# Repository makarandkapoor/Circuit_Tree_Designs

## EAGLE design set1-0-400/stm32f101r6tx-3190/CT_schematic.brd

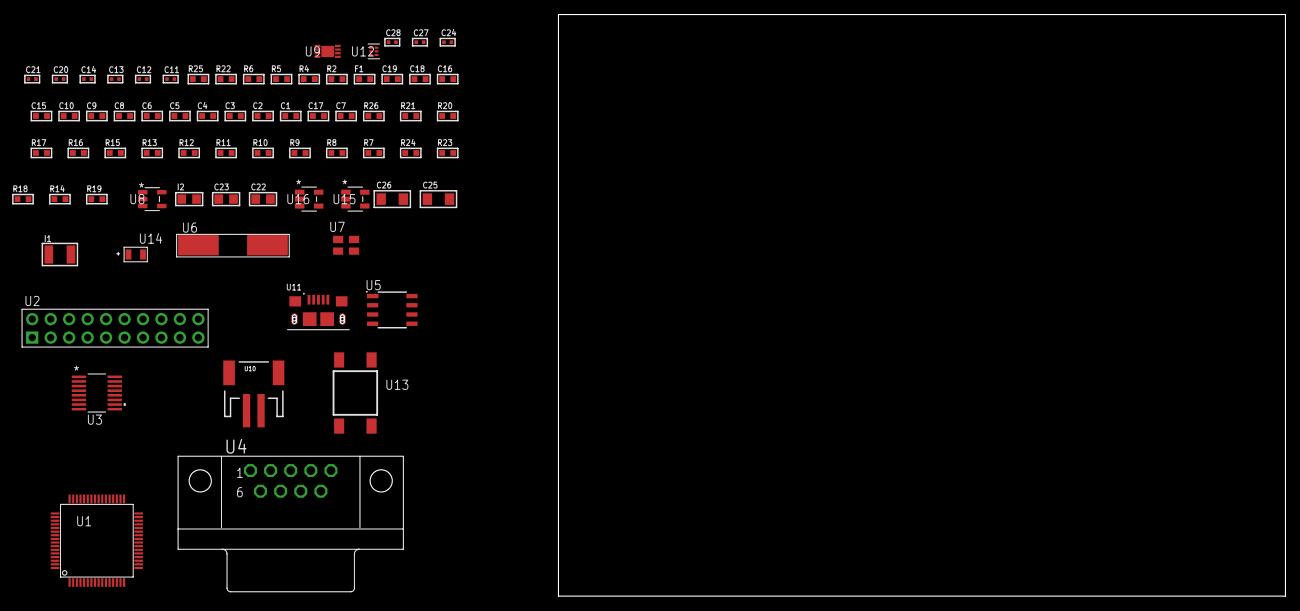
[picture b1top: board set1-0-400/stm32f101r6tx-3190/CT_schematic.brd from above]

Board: 2 copper layers, 71 parts (0 on the bottom side), 44 nets, no tracks yet.

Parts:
C1, C10, C15, C16, C18, C19: 1e-06; C0603
C2, C3, C4, C5, C6: 1e-07; C0603
C7: 4.7e-06; C0603
C8, C9: 1e-08; C0603
C11, C12: 1e-11; C0402
C13, C14, C24: 1e-07; C0402
C17: 2.2e-07; C0603
C20, C21, C27, C28: 1e-08; C0402
C22, C23: 1e-05; C0805
C25, C26: 1e-05; C1206
F1: 240.0; L0603
I1: 1e-05; L1210
I2: 2.2e-06; L0805
R2: 1000.0; R0603
R4: 4700.0; R0603
R5, R6: 2200.0; R0603
R7, R8, R9, R10, R11, R12, R13, R15, R16, R17, R20, R21, R26: 10000.0; R0603
R14: 100000.0; R0603
R18: 220000.0; R0603
R19: 1000000.0; R0603
R22: 9100.0; R0603
R23: 680000.0; R0603
R24: 120000.0; R0603
R25: 2000.0; R0603
U1: STM32F101R6T6; LQFP64
U2: TST-110-05-T-D-RA
U3: LTC2804CGN-1#PBF; SSOP-16
U4: 182-009-113R531; 182-009-MALE
U5: 24AA1025T-I/SN; SOIC-8
U6: ABLS-25.000MHZ-B2F-T
U7: ASEK-32.768KHz-ECST; ASEK
U8: ltc3406es5; TSOT-23-5
U9: MCP73831T-2ACI/MC; DFN8_2X3MC
U10: S2B-PH-SM4-TB(LF)(SN); JST-2-SMD
U11: 10118193-0001LF; FCI_10118193-0001LF
U12: TPS3895ADRYR; SON-6
U13: 4-1437565-2; SW_4-1437565-2
U14: Q65110A2395; LGM67K-G1J2-24-Z
U15, U16: nc7sz125m5x; NC7SZ125M5X

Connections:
CLK_CRYSTAL_U1_5: C11.1, U1.5, U6.1
CLK_CRYSTAL_U1_6: C12.1, U1.6, U6.2
CLK_U1_3: U1.3, U7.3
GND: C1.2, C2.2, C3.2, C4.2, C5.2, C6.2, C7.2, C8.2, C9.2, C10.2, C11.2, C12.2, C13.2, C14.2, C15.2, C16.2, C18.2, C19.2, C20.2, C21.2, C22.2, C23.1, C23.2, C24.2, C25.2, C26.2, C27.2, C28.2, R2.2, R7.2, R13.2, R16.2, R18.2, R22.2, R24.2, R25.2, U1.12, U1.18, U1.31, U1.47, U1.63, U2.4, U2.6, U2.8, U2.10, U2.12, U2.14, U2.16, U2.18, U2.20, U3.8, U4.5, U5.4, U5.7, U7.2, U8.2, U9.6, U9.9, U10.2, U11.5, U11.6, U11.7, U11.8, U11.9, U12.2, U14.C, U15.2, U15.3, U16.1, U16.3
INPUT_USBPOWER_5V: C25.1, R26.2, U9.1, U9.2, U11.1
NET_U1_7: R4.1, U1.7, U16.4
NET_U1_13: C8.1, C9.1, C10.1, F1.1, U1.13
NET_U1_58: R5.1, U1.58, U5.6
NET_U1_59: R6.1, U1.59, U5.5
NET_U1_60: R7.1, U1.60
NET_U1_62: U13.3, U13.4
NET_U2_3: R8.1, U2.3
NET_U2_7: R10.1, U2.7
NET_U2_9: R11.1, U2.9
NET_U2_19: R13.1, U2.19
NET_U3_6: C15.1, U3.6
NET_U3_7: C17.1, I1.2, U3.7
NET_U3_9: C16.1, U3.9
NET_U3_10: C17.2, U3.10
NET_U3_11: R14.1, U3.11
NET_U4_2: U3.1, U4.2
NET_U4_3: U3.3, U4.3
NET_U4_7: U3.2, U4.7
NET_U4_8: U3.4, U4.8
NET_U5_1: R16.1, U5.1
NET_U5_2: R17.1, U5.2
NET_U5_3: R15.1, U5.3
NET_U8_3: I2.1, U8.3
NET_U8_5: R18.1, R19.1, U8.5
NET_U8_ATNET_3: I2.2, R19.2
NET_U9_5: R26.1, U9.5
NET_U9_8: R25.1, U9.8
NET_U12_1: R21.1, R22.1, U12.1
NET_U12_3: R23.2, R24.1, U12.3
NET_U12_4: R20.1, U12.4, U15.4, U16.2
NET_U13_1: R2.1, U13.1, U13.2
PROC_SYS_JTDI: R9.1, U1.50, U2.5
PROC_SYS_JTDO_TRACESWO: U1.55, U2.13
PROC_USART1_CTS: U1.44, U3.13
PROC_USART1_RX: U1.43, U3.16
PROC_USART1_TX: U1.42, U3.14
RST_OUT_U2_SRESET_B: R12.1, U2.15, U15.1
VCC_S1_3V7: C22.1, C26.1, U8.4, U9.3, U9.4, U10.1
VCC_TIER1_3V3: C1.1, C2.1, C3.1, C4.1, C5.1, C6.1, C7.1, C13.1, C14.1, C18.1, C19.1, C20.1, C21.1, C23.2, C24.1, C27.1, C28.1, F1.2, I1.1, I2.2, R4.2, R5.2, R6.2, R8.2, R9.2, R10.2, R11.2, R12.2, R14.2, R15.2, R17.2, R19.2, R20.2, R21.2, R23.1, U1.1, U1.19, U1.32, U1.48, U1.64, U2.1, U2.2, U3.5, U3.12, U5.8, U7.4, U12.6, U15.5, U16.5

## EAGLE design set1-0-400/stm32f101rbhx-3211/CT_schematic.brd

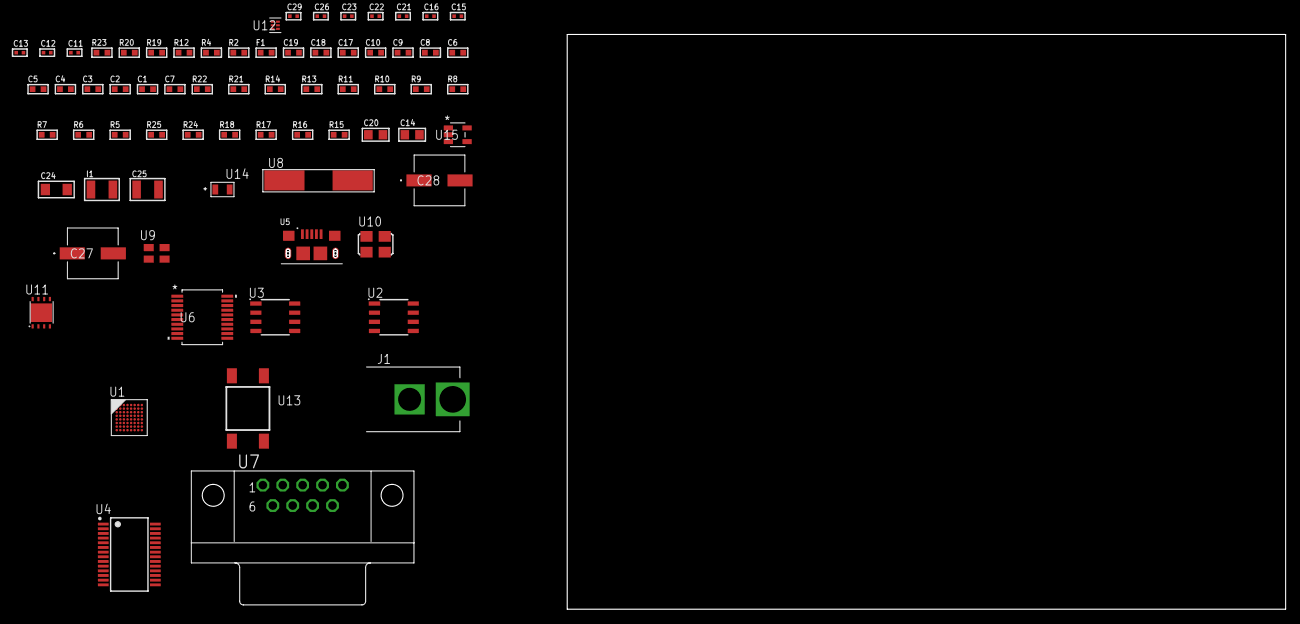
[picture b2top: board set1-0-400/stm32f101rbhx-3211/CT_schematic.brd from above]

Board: 2 copper layers, 70 parts (0 on the bottom side), 55 nets, no tracks yet.

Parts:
C1, C10, C17, C18, C19: 1e-06; C0603
C2, C3, C4, C5, C6: 1e-07; C0603
C7: 4.7e-06; C0603
C8, C9: 1e-08; C0603
C11, C12, C21, C22, C23, C29: 1e-08; C0402
C13, C15, C16, C26: 1e-07; C0402
C14, C20: 4.7e-06; C0805
C24: 1e-05; C1206
C25: 1e-05; C1210
C27, C28: 0.0001; EXV-9H
F1: 240.0; L0603
I1: 1.5e-05; L1210
J1: PJ-037B; PJ-037B_PACKAGE
R2, R20: 1000.0; R0603
R4, R12: 4700.0; R0603
R5, R6, R7, R8, R9, R10, R11, R13, R14, R21, R22: 10000.0; R0603
R15, R16, R17, R18: 100000.0; R0603
R19: 2231.0; R0603
R23: 9100.0; R0603
R24: 680000.0; R0603
R25: 120000.0; R0603
U1: STM32F101RBH6; TFBGA64
U2: AT25010B-SSHL-T; SOIC-8
U3: AT25M01-SSHM-T; SOIC-8
U4: FT232RL-REEL; SSOP-28
U5: 10118193-0001LF; FCI_10118193-0001LF
U6: MAX3218EAP+T; SSOP-20
U7: 182-009-113R531; 182-009-MALE
U8: ABLS-12.000MHZ-B4-T
U9: ASEK-32.768KHz-ECST; ASEK
U10: ASFL1-25MHZ-NCS; ASFL1
U11: LP3878SDX-ADJ/NOPB; WSON-8
U12: TPS3895ADRYR; SON-6
U13: 4-1437565-2; SW_4-1437565-2
U14: Q65110A2395; LGM67K-G1J2-24-Z
U15: nc7sz125m5x; NC7SZ125M5X

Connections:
CLK_CRYSTAL_U4_27: U4.27, U8.1
CLK_CRYSTAL_U4_28: U4.28, U8.2
CLK_U1_A1: U1.A1, U9.3
CLK_U1_C1: U1.C1, U10.3
GND: C1.2, C2.2, C3.2, C4.2, C5.2, C6.2, C7.2, C8.2, C9.2, C10.2, C11.2, C12.2, C13.2, C14.2, C15.2, C16.2, C17.2, C18.2, C19.2, C21.2, C22.2, C23.2, C24.2, C25.2, C26.2, C27.2, C28.2, C29.2, J1.2, R2.2, R5.2, R14.2, R20.2, R23.2, R25.2, U1.C2, U1.D4, U1.D5, U1.D6, U1.F1, U2.4, U3.4, U4.7, U4.18, U4.21, U4.25, U4.26, U5.5, U5.6, U5.7, U5.8, U5.9, U6.5, U6.17, U6.20, U7.5, U9.2, U10.2, U11.3, U11.PAD, U12.2, U14.C, U15.1, U15.3
NET_U1_B4: R5.1, U1.B4
NET_U1_E1: R4.1, U1.E1, U15.4
NET_U1_H1: C8.1, C9.1, C10.1, F1.1, U1.G1, U1.H1
NET_U1_H7: U13.3, U13.4
NET_U2_3: R6.1, U2.3
NET_U2_7: R8.1, U2.7
NET_U3_3: R9.1, U3.3
NET_U3_7: R11.1, U3.7
NET_U4_14: R13.1, U4.14
NET_U4_17: C15.1, U4.17
NET_U4_19: R14.1, U4.19
NET_U5_1: R12.1, U5.1
NET_U5_2: U4.16, U5.2
NET_U5_3: U4.15, U5.3
NET_U6_1: I1.1, U6.1
NET_U6_2: R15.1, U6.2
NET_U6_3: R16.1, U6.3
NET_U6_4: R17.1, U6.4
NET_U6_15: C19.1, U6.15
NET_U6_16: C20.2, U6.16
NET_U6_18: C20.1, U6.18
NET_U6_19: C18.1, U6.19
NET_U7_2: U6.12, U7.2
NET_U7_3: U6.14, U7.3
NET_U7_7: U6.11, U7.7
NET_U7_8: U6.13, U7.8
NET_U11_1: C23.1, U11.1
NET_U11_6: R19.2, R20.1, U11.6
NET_U11_8: R18.1, U11.8
NET_U12_1: R22.1, R23.1, U12.1
NET_U12_3: R24.2, R25.1, U12.3
NET_U12_4: R21.1, U12.4, U15.2
NET_U13_1: R2.1, U13.1, U13.2
PROC_SPI1_MISO: U1.A4, U3.2
PROC_SPI1_MOSI: U1.C4, U3.5
PROC_SPI1_NSS: R10.1, U1.A6, U3.1
PROC_SPI1_SCK: U1.A5, U3.6
PROC_SPI2_MISO: U1.F8, U2.2
PROC_SPI2_MOSI: U1.F7, U2.5
PROC_SPI2_NSS: R7.1, U1.H8, U2.1
PROC_SPI2_SCK: U1.G8, U2.6
PROC_USART1_CTS: U1.C8, U6.8
PROC_USART1_RX: U1.C3, U6.9
PROC_USART1_TX: U1.C7, U6.7
PROC_USART2_CTS: U1.G2, U4.3
PROC_USART2_RTS: U1.H2, U4.11
PROC_USART2_RX: U1.G3, U4.1
PROC_USART2_TX: U1.F3, U4.5
VCC_S1_7V2: C24.1, C27.1, C28.1, J1.1, R18.2, U11.4
VCC_TIER1_3V3: C1.1, C2.1, C3.1, C4.1, C5.1, C6.1, C7.1, C11.1, C12.1, C13.1, C14.1, C16.1, C17.1, C21.1, C22.1, C25.1, C26.1, C29.1, F1.2, I1.2, R4.2, R6.2, R7.2, R8.2, R9.2, R10.2, R11.2, R13.2, R15.2, R16.2, R17.2, R19.1, R21.2, R22.2, R24.1, U1.B2, U1.D2, U1.E4, U1.E5, U1.E6, U2.8, U3.8, U4.4, U4.20, U6.6, U9.4, U10.4, U11.5, U12.6, U15.5

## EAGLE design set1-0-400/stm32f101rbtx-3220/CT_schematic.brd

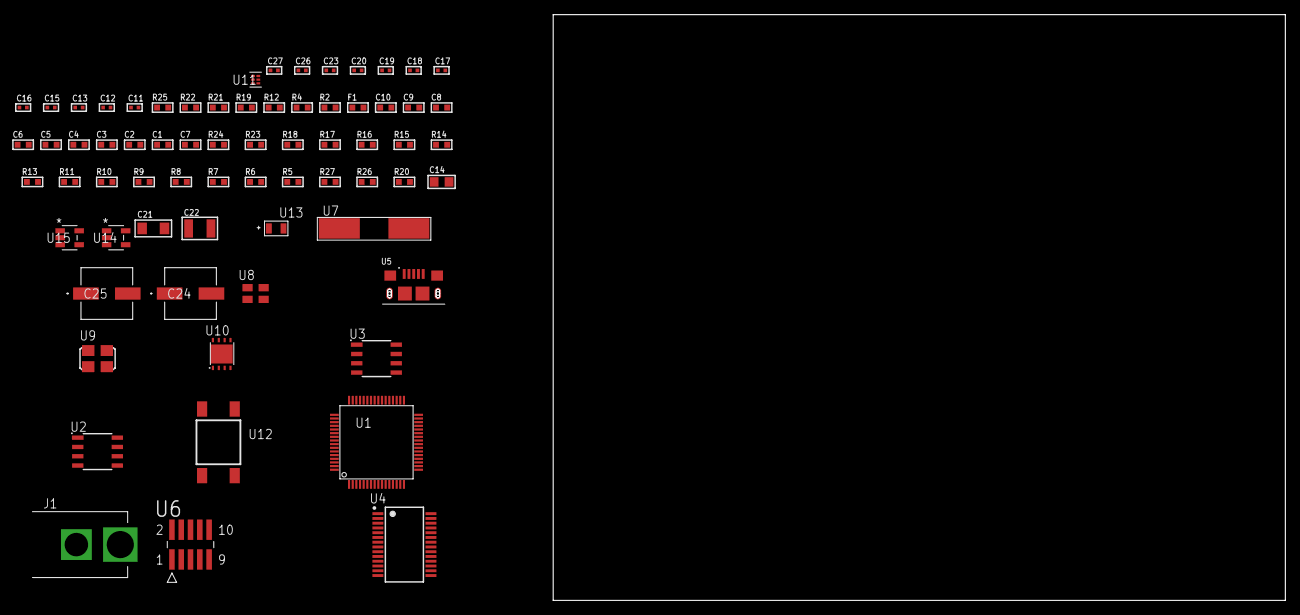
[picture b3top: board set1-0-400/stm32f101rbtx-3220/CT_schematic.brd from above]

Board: 2 copper layers, 122.6 x 80.0 mm, 69 parts (0 on the bottom side), 45 nets, no tracks yet.

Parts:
C1, C10: 1e-06; C0603
C2, C3, C4, C5, C6: 1e-07; C0603
C7: 4.7e-06; C0603
C8, C9: 1e-08; C0603
C11, C12, C18, C19, C20, C26, C27: 1e-08; C0402
C13, C15, C16, C17, C23: 1e-07; C0402
C14: 4.7e-06; C0805
C21: 1e-05; C1206
C22: 1e-05; C1210
C24, C25: 0.0001; EXV-9H
F1: 240.0; L0603
J1: PJ-037B; PJ-037B_PACKAGE
R2, R22: 1000.0; R0603
R4, R12: 4700.0; R0603
R5, R6, R7, R8, R9, R10, R11, R13, R14, R15, R16, R17, R18, R23, R24: 10000.0; R0603
R19: 5.0; R0603
R20: 100000.0; R0603
R21: 2231.0; R0603
R25: 9100.0; R0603
R26: 680000.0; R0603
R27: 120000.0; R0603
U1: STM32F101RBT6; LQFP64
U2: AT25020B-SSHL-T; SOIC-8
U3: AT25040B-SSHL-T; SOIC-8
U4: FT232RL-REEL; SSOP-28
U5: 10118193-0001LF; FCI_10118193-0001LF
U6: FTSH-105-01-L-DV-K; SAMTEC_FTSH-105-01-L-DV-K
U7: ABLS-12.000MHZ-B4-T
U8: ASEK-32.768KHz-ECST; ASEK
U9: ASFL1-25MHZ-NCS; ASFL1
U10: LP3878SDX-ADJ/NOPB; WSON-8
U11: TPS3895ADRYR; SON-6
U12: 4-1437565-2; SW_4-1437565-2
U13: Q65110A2395; LGM67K-G1J2-24-Z
U14, U15: nc7sz125m5x; NC7SZ125M5X

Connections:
CLK_CRYSTAL_U4_27: U4.27, U7.1
CLK_CRYSTAL_U4_28: U4.28, U7.2
CLK_U1_3: U1.3, U8.3
CLK_U1_5: U1.5, U9.3
GND: C1.2, C2.2, C3.2, C4.2, C5.2, C6.2, C7.2, C8.2, C9.2, C10.2, C11.2, C12.2, C13.2, C14.2, C15.2, C16.2, C17.2, C18.2, C19.2, C20.2, C21.2, C22.2, C23.2, C24.2, C25.2, C26.2, C27.2, J1.2, R2.2, R5.2, R14.2, R18.2, R19.2, R22.2, R25.2, R27.2, U1.12, U1.18, U1.31, U1.47, U1.63, U2.4, U3.4, U4.7, U4.18, U4.21, U4.25, U4.26, U5.5, U5.6, U5.7, U5.8, U5.9, U6.3, U6.5, U8.2, U9.2, U10.3, U10.PAD, U11.2, U13.C, U14.2, U14.3, U15.1, U15.3
NET_U1_7: R4.1, U1.7, U15.4
NET_U1_13: C8.1, C9.1, C10.1, F1.1, U1.13
NET_U1_60: R5.1, U1.60
NET_U1_62: U12.3, U12.4
NET_U2_3: R6.1, U2.3
NET_U2_7: R8.1, U2.7
NET_U3_3: R9.1, U3.3
NET_U3_7: R11.1, U3.7
NET_U4_14: R13.1, U4.14
NET_U4_17: C15.1, U4.17
NET_U4_19: R14.1, U4.19
NET_U5_1: R12.1, U5.1
NET_U5_2: U4.16, U5.2
NET_U5_3: U4.15, U5.3
NET_U6_2: R17.1, U6.2
NET_U6_4: R18.1, U6.4
NET_U6_9: R19.1, U6.9
NET_U10_1: C20.1, U10.1
NET_U10_6: R21.2, R22.1, U10.6
NET_U10_8: R20.1, U10.8
NET_U11_1: R24.1, R25.1, U11.1
NET_U11_3: R26.2, R27.1, U11.3
NET_U11_4: R23.1, U11.4, U14.4, U15.2
NET_U12_1: R2.1, U12.1, U12.2
PROC_SPI1_MISO: U1.22, U3.2
PROC_SPI1_MOSI: U1.23, U3.5
PROC_SPI1_NSS: R10.1, U1.20, U3.1
PROC_SPI1_SCK: U1.21, U3.6
PROC_SPI2_MISO: U1.35, U2.2
PROC_SPI2_MOSI: U1.36, U2.5
PROC_SPI2_NSS: R7.1, U1.33, U2.1
PROC_SPI2_SCK: U1.34, U2.6
PROC_SYS_JTDI: R16.1, U1.50, U6.8
PROC_SYS_JTDO_TRACESWO: U1.55, U6.6
PROC_USART1_CTS: U1.44, U4.3
PROC_USART1_RX: U1.43, U4.1
PROC_USART1_TX: U1.42, U4.5
RST_OUT_U6_JTAG_RST_B: R15.1, U6.10, U14.1
VCC_S1_5V8: C21.1, C24.1, C25.1, J1.1, R20.2, U10.4
VCC_TIER1_3V3: C1.1, C2.1, C3.1, C4.1, C5.1, C6.1, C7.1, C11.1, C12.1, C13.1, C14.1, C16.1, C17.1, C18.1, C19.1, C22.1, C23.1, C26.1, C27.1, F1.2, R4.2, R6.2, R7.2, R8.2, R9.2, R10.2, R11.2, R13.2, R15.2, R16.2, R17.2, R21.1, R23.2, R24.2, R26.1, U1.1, U1.19, U1.32, U1.48, U1.64, U2.8, U3.8, U4.4, U4.20, U6.1, U8.4, U9.4, U10.5, U11.6, U14.5, U15.5

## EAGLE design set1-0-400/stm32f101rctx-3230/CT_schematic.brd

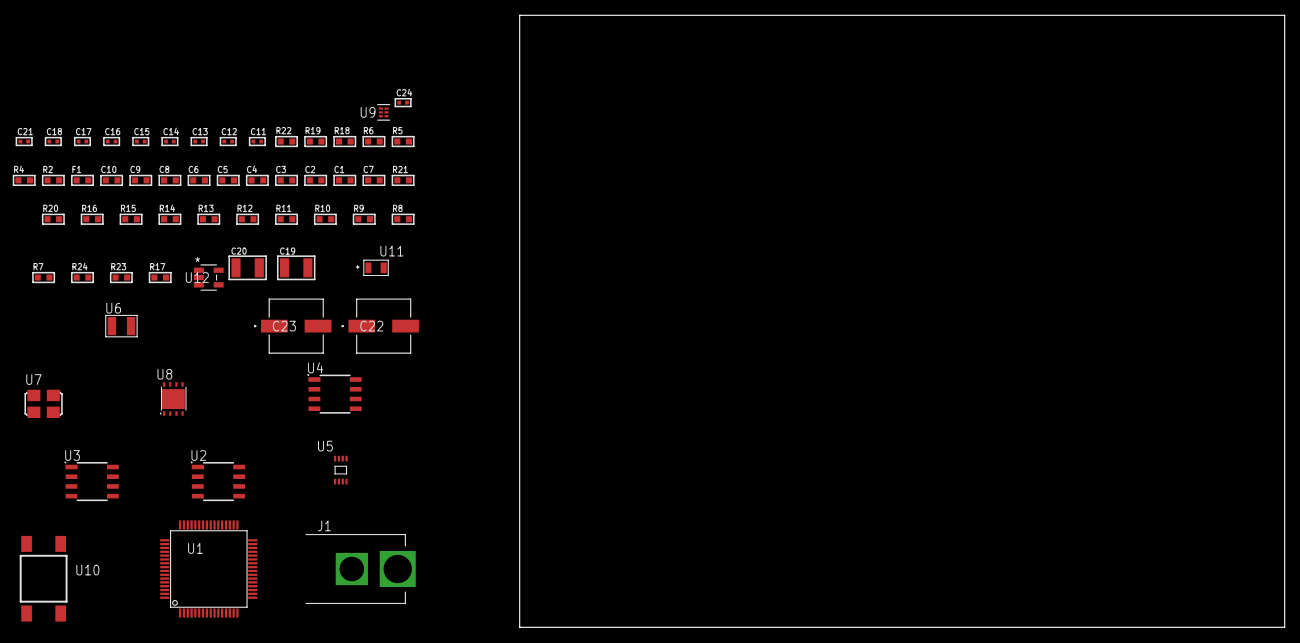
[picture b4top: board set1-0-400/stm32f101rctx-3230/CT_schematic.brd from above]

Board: 2 copper layers, 100.0 x 80.0 mm, 60 parts (0 on the bottom side), 37 nets, no tracks yet.

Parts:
C1, C10: 1e-06; C0603
C2, C3, C4, C5, C6: 1e-07; C0603
C7: 4.7e-06; C0603
C8, C9: 1e-08; C0603
C11, C12: 1e-11; C0402
C13, C14, C15, C16, C17, C18, C24: 1e-08; C0402
C19, C20: 1e-05; C1210
C21: 1e-07; C0402
C22, C23: 0.0001; EXV-9H
F1: 240.0; L0603
J1: PJ-037B; PJ-037B_PACKAGE
R2, R19: 1000.0; R0603
R4: 4700.0; R0603
R5, R6: 2200.0; R0603
R7, R8, R9, R10, R11, R12, R13, R14, R15, R16, R20, R21: 10000.0; R0603
R17: 100000.0; R0603
R18: 2231.0; R0603
R22: 9100.0; R0603
R23: 680000.0; R0603
R24: 120000.0; R0603
U1: STM32F101RCT6; LQFP64
U2: AT25010B-SSHL-T; SOIC-8
U3: AT25040B-SSHL-T; SOIC-8
U4: AT25M01-SSHM-T; SOIC-8
U5: 24AA08T-I/MNY; TDFN-8/6MM
U6: ABS07-32.768KHZ-7-T
U7: ASFL1-25MHZ-NCS; ASFL1
U8: LP3878SDX-ADJ/NOPB; WSON-8
U9: TPS3895ADRYR; SON-6
U10: 4-1437565-2; SW_4-1437565-2
U11: Q65110A2395; LGM67K-G1J2-24-Z
U12: nc7sz125m5x; NC7SZ125M5X

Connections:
CLK_CRYSTAL_U1_3: C11.1, U1.3, U6.1
CLK_CRYSTAL_U1_4: C12.1, U1.4, U6.2
CLK_U1_5: U1.5, U7.3
GND: C1.2, C2.2, C3.2, C4.2, C5.2, C6.2, C7.2, C8.2, C9.2, C10.2, C11.2, C12.2, C13.2, C14.2, C15.2, C16.2, C17.2, C18.2, C19.2, C20.2, C21.2, C22.2, C23.2, C24.2, J1.2, R2.2, R7.2, R19.2, R22.2, R24.2, U1.12, U1.18, U1.31, U1.47, U1.63, U2.4, U3.4, U4.4, U5.4, U5.7, U7.2, U8.3, U8.PAD, U9.2, U11.C, U12.1, U12.3
NET_U1_7: R4.1, U1.7, U12.4
NET_U1_13: C8.1, C9.1, C10.1, F1.1, U1.13
NET_U1_58: R5.1, U1.58, U5.6
NET_U1_59: R6.1, U1.59, U5.5
NET_U1_60: R7.1, U1.60
NET_U1_62: U10.3, U10.4
NET_U2_3: R8.1, U2.3
NET_U2_7: R10.1, U2.7
NET_U3_3: R11.1, U3.3
NET_U3_7: R13.1, U3.7
NET_U4_3: R14.1, U4.3
NET_U4_7: R16.1, U4.7
NET_U8_1: C18.1, U8.1
NET_U8_6: R18.2, R19.1, U8.6
NET_U8_8: R17.1, U8.8
NET_U9_1: R21.1, R22.1, U9.1
NET_U9_3: R23.2, R24.1, U9.3
NET_U9_4: R20.1, U9.4, U12.2
NET_U10_1: R2.1, U10.1, U10.2
PROC_SPI1_MISO: U1.22, U4.2
PROC_SPI1_MOSI: U1.23, U4.5
PROC_SPI1_NSS: R15.1, U1.20, U4.1
PROC_SPI1_SCK: U1.21, U4.6
PROC_SPI2_MISO: U1.35, U3.2
PROC_SPI2_MOSI: U1.36, U3.5
PROC_SPI2_NSS: R12.1, U1.33, U3.1
PROC_SPI2_SCK: U1.34, U3.6
PROC_SPI3_MISO: U1.56, U2.2
PROC_SPI3_MOSI: U1.57, U2.5
PROC_SPI3_NSS: R9.1, U1.50, U2.1
PROC_SPI3_SCK: U1.55, U2.6
VCC_S1_14V4: C19.1, C22.1, C23.1, J1.1, R17.2, U8.4
VCC_TIER1_3V3: C1.1, C2.1, C3.1, C4.1, C5.1, C6.1, C7.1, C13.1, C14.1, C15.1, C16.1, C17.1, C20.1, C21.1, C24.1, F1.2, R4.2, R5.2, R6.2, R8.2, R9.2, R10.2, R11.2, R12.2, R13.2, R14.2, R15.2, R16.2, R18.1, R20.2, R21.2, R23.1, U1.1, U1.19, U1.32, U1.48, U1.64, U2.8, U3.8, U4.8, U5.8, U7.4, U8.5, U9.6, U12.5

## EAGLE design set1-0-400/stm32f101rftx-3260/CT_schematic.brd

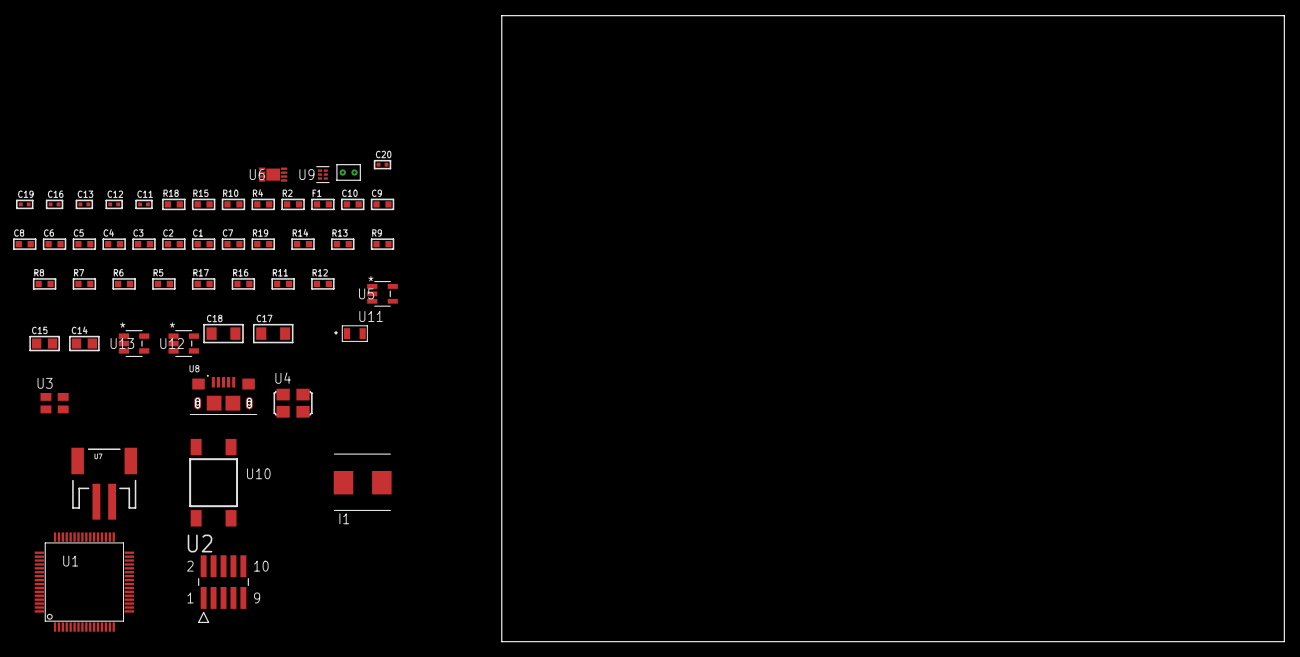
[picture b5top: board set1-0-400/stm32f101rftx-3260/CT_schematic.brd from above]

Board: 2 copper layers, 53 parts (0 on the bottom side), 26 nets, no tracks yet.

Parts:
C1, C10: 1e-06; C0603
C2, C3, C4, C5, C6: 1e-07; C0603
C7: 4.7e-06; C0603
C8, C9: 1e-08; C0603
C11, C16: 1e-07; C0402
C12, C13, C19, C20: 1e-08; C0402
C14, C15: 1e-05; C0805
C17, C18: 1e-05; C1206
F1: 240.0; L0603
I1: 2e-06; WE-HCI_7030/7040/7050
R2: 1000.0; R0603
R4: 4700.0; R0603
R5, R6, R7, R8, R9, R13, R14, R19: 10000.0; R0603
R10: 5.0; R0603
R11: 220000.0; R0603
R12: 1000000.0; R0603
R15: 9100.0; R0603
R16: 680000.0; R0603
R17: 120000.0; R0603
R18: 2000.0; R0603
U1: STM32F101RFT6; LQFP64
U2: FTSH-105-01-L-DV-K; SAMTEC_FTSH-105-01-L-DV-K
U3: ASEK-32.768KHz-ECST; ASEK
U4: ASFL1-25MHZ-NCS; ASFL1
U5: ltc3406es5; TSOT-23-5
U6: MCP73831T-2ACI/MC; DFN8_2X3MC
U7: S2B-PH-SM4-TB(LF)(SN); JST-2-SMD
U8: 10118193-0001LF; FCI_10118193-0001LF
U9: TPS3895ADRYR; SON-6
U10: 4-1437565-2; SW_4-1437565-2
U11: Q65110A2395; LGM67K-G1J2-24-Z
U12, U13: nc7sz125m5x; NC7SZ125M5X
U14: Dummy; DUMMY_PACKAGE_113

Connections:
CLK_U1_3: U1.3, U3.3
CLK_U1_5: U1.5, U4.3
GND: C1.2, C2.2, C3.2, C4.2, C5.2, C6.2, C7.2, C8.2, C9.2, C10.2, C11.2, C12.2, C13.2, C14.2, C15.1, C15.2, C16.2, C17.2, C18.2, C19.2, C20.2, R2.2, R5.2, R9.2, R10.2, R11.2, R15.2, R17.2, R18.2, U1.12, U1.18, U1.31, U1.47, U1.63, U2.3, U2.5, U3.2, U4.2, U5.2, U6.6, U6.9, U7.2, U8.5, U8.6, U8.7, U8.8, U8.9, U9.2, U11.C, U12.2, U12.3, U13.1, U13.3, U14.1
INPUT_USBPOWER_5V: C17.1, R19.2, U6.1, U6.2, U8.1
NET_U1_7: R4.1, U1.7, U13.4
NET_U1_13: C8.1, C9.1, C10.1, F1.1, U1.13
NET_U1_60: R5.1, U1.60
NET_U1_62: U10.3, U10.4
NET_U2_2: R8.1, U2.2
NET_U2_4: R9.1, U2.4
NET_U2_9: R10.1, U2.9
NET_U5_3: I1.1, U5.3
NET_U5_5: R11.1, R12.1, U5.5
NET_U5_ATNET_3: I1.2, R12.2
NET_U6_5: R19.1, U6.5
NET_U6_8: R18.1, U6.8
NET_U9_1: R14.1, R15.1, U9.1
NET_U9_3: R16.2, R17.1, U9.3
NET_U9_4: R13.1, U9.4, U12.4, U13.2
NET_U10_1: R2.1, U10.1, U10.2
PROC_DAC_OUT2: U1.21, U14.2
PROC_SYS_JTDI: R7.1, U1.50, U2.8
PROC_SYS_JTDO_TRACESWO: U1.55, U2.6
RST_OUT_U2_JTAG_RST_B: R6.1, U2.10, U12.1
VCC_S1_3V7: C14.1, C18.1, U5.4, U6.3, U6.4, U7.1
VCC_TIER1_3V3: C1.1, C2.1, C3.1, C4.1, C5.1, C6.1, C7.1, C11.1, C12.1, C13.1, C15.2, C16.1, C19.1, C20.1, F1.2, I1.2, R4.2, R6.2, R7.2, R8.2, R12.2, R13.2, R14.2, R16.1, U1.1, U1.19, U1.32, U1.48, U1.64, U2.1, U3.4, U4.4, U9.6, U12.5, U13.5

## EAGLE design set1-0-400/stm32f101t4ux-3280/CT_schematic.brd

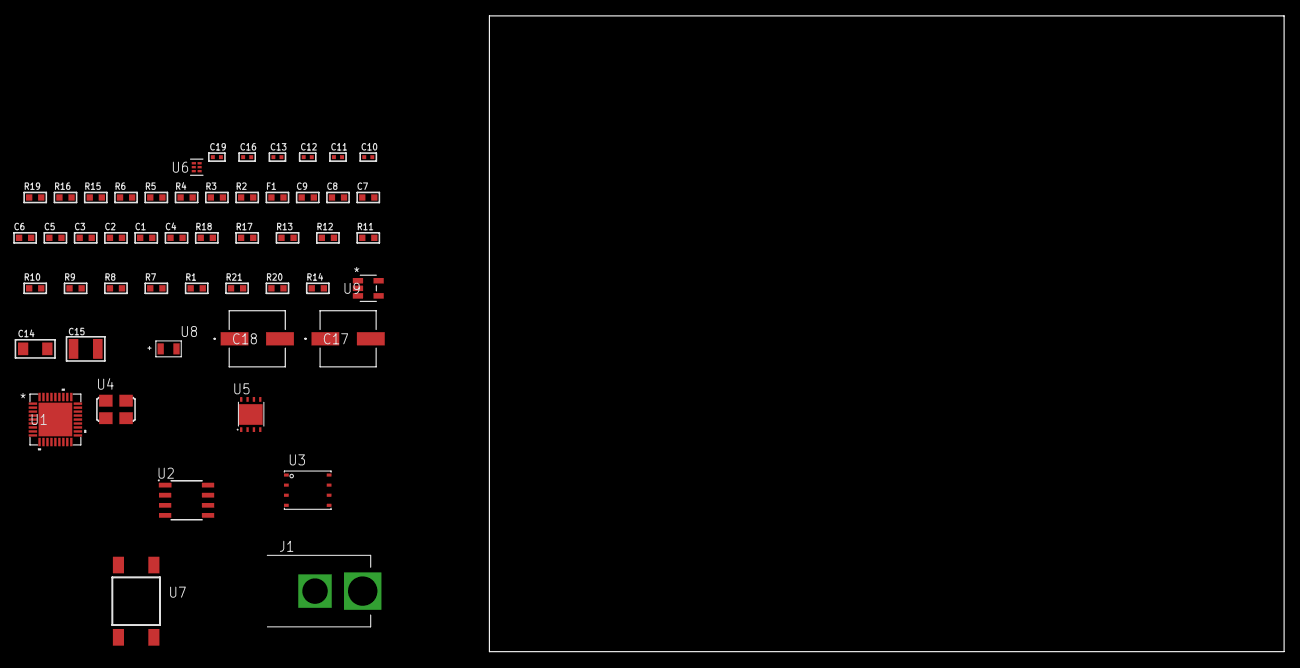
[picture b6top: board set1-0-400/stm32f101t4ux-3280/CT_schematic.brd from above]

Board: 2 copper layers, 100.0 x 80.0 mm, 51 parts (0 on the bottom side), 27 nets, no tracks yet.

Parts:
C1, C2, C3, C5, C6: 1e-07; C0603
C4: 4.7e-06; C0603
C7, C8: 1e-08; C0603
C9: 1e-06; C0603
C10, C11, C12, C13, C19: 1e-08; C0402
C14: 1e-05; C1206
C15: 1e-05; C1210
C16: 1e-07; C0402
C17, C18: 0.0001; EXV-9H
F1: 240.0; L0603
J1: PJ-037B; PJ-037B_PACKAGE
R1, R7, R8, R9, R10, R11, R12, R13, R17, R18: 10000.0; R0603
R2, R16: 1000.0; R0603
R3: 1600.5; R0603
R4: 4700.0; R0603
R5, R6: 2200.0; R0603
R14: 100000.0; R0603
R15: 2231.0; R0603
R19: 9100.0; R0603
R20: 680000.0; R0603
R21: 120000.0; R0603
U1: STM32F101T4U6; VFQFPN36
U2: AT25640B-SSHL-T; SOIC-8
U3: 24AA256-I/MF; DFN8-S
U4: ASFL1-25MHZ-NCS; ASFL1
U5: LP3878SDX-ADJ/NOPB; WSON-8
U6: TPS3895ADRYR; SON-6
U7: 4-1437565-2; SW_4-1437565-2
U8: Q65110A2395; LGM67K-G1J2-24-Z
U9: nc7sz125m5x; NC7SZ125M5X

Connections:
CLK_U1_2: U1.2, U4.3
GND: C1.2, C2.2, C3.2, C4.2, C5.2, C6.2, C7.2, C8.2, C9.2, C10.2, C11.2, C12.2, C13.2, C14.2, C15.2, C16.2, C17.2, C18.2, C19.2, J1.2, R2.2, R7.2, R12.2, R13.2, R16.2, R19.2, R21.2, U1.5, U1.18, U1.26, U1.36, U1.37, U2.4, U3.4, U4.2, U5.3, U5.PAD, U6.2, U8.C, U9.1, U9.3
NET_U1_4: R4.1, U1.4, U9.4
NET_U1_6: C7.1, C8.1, C9.1, F1.1, U1.6
NET_U1_31: R3.1, U1.31, U8.A
NET_U1_32: R1.1, U1.32, U7.3, U7.4
NET_U1_33: R5.1, U1.33, U3.6
NET_U1_34: R6.1, U1.34, U3.5
NET_U1_35: R7.1, U1.35
NET_U2_3: R8.1, U2.3
NET_U2_7: R10.1, U2.7
NET_U3_1: R11.1, U3.1
NET_U3_2: R12.1, U3.2
NET_U3_3: R13.1, U3.3
NET_U5_1: C13.1, U5.1
NET_U5_6: R15.2, R16.1, U5.6
NET_U5_8: R14.1, U5.8
NET_U6_1: R18.1, R19.1, U6.1
NET_U6_3: R20.2, R21.1, U6.3
NET_U6_4: R17.1, U6.4, U9.2
NET_U7_1: R2.1, U7.1, U7.2
PROC_SPI1_MISO: U1.13, U2.2
PROC_SPI1_MOSI: U1.14, U2.5
PROC_SPI1_NSS: R9.1, U1.11, U2.1
PROC_SPI1_SCK: U1.12, U2.6
VCC_S1_6V4: C14.1, C17.1, C18.1, J1.1, R14.2, U5.4
VCC_TIER1_3V3: C1.1, C2.1, C3.1, C4.1, C5.1, C6.1, C10.1, C11.1, C12.1, C15.1, C16.1, C19.1, F1.2, R1.2, R3.2, R4.2, R5.2, R6.2, R8.2, R9.2, R10.2, R11.2, R15.1, R17.2, R18.2, R20.1, U1.1, U1.19, U1.27, U2.8, U3.7, U3.8, U4.4, U5.5, U6.6, U9.5

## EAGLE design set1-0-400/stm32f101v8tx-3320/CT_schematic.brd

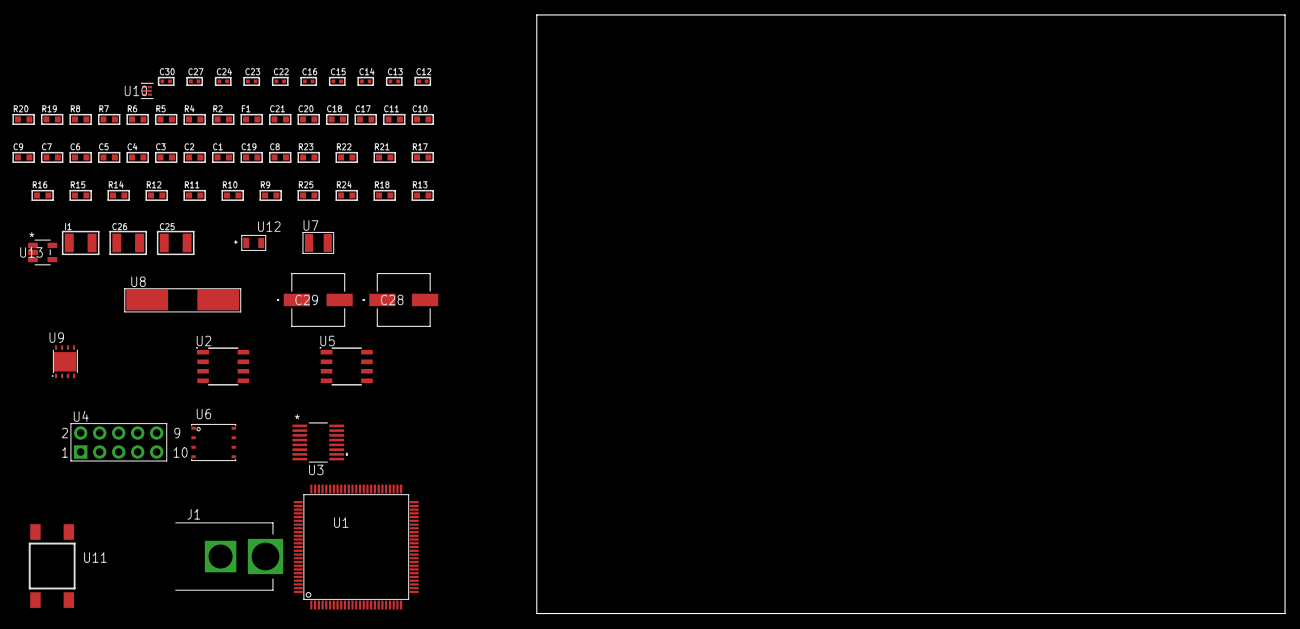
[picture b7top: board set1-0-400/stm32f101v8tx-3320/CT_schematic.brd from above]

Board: 2 copper layers, 100.0 x 80.0 mm, 69 parts (0 on the bottom side), 44 nets, no tracks yet.

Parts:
C1, C11, C17, C18, C20, C21: 1e-06; C0603
C2, C3, C4, C5, C6, C7: 1e-07; C0603
C8: 4.7e-06; C0603
C9, C10: 1e-08; C0603
C12, C13, C14, C15: 1e-11; C0402
C16, C22, C23, C24, C30: 1e-08; C0402
C19: 2.2e-07; C0603
C25, C26: 1e-05; C1210
C27: 1e-07; C0402
C28, C29: 0.0001; EXV-9H
F1: 240.0; L0603
I1: 1e-05; L1210
J1: PJ-037B; PJ-037B_PACKAGE
R2, R20: 1000.0; R0603
R4: 4700.0; R0603
R5, R6, R7, R8: 2200.0; R0603
R9, R10, R11, R12, R14, R15, R16, R17, R21, R22: 10000.0; R0603
R13, R18: 100000.0; R0603
R19: 1500.0; R0603
R23: 18000.0; R0603
R24: 470000.0; R0603
R25: 120000.0; R0603
U1: STM32F101V8T6; LQFP100
U2: AT25080B-SSHL-T; SOIC-8
U3: LTC2804CGN-1#PBF; SSOP-16
U4: HTSS-105-01-G-D
U5: M24M02-DRMN6TP; SOIC-8
U6: 24AA512-I/MF; DFN8-S
U7: ABS07-32.768KHZ-7-T
U8: ABLS-25.000MHZ-B2F-T
U9: LP3878SDX-ADJ/NOPB; WSON-8
U10: TPS3895ADRYR; SON-6
U11: 4-1437565-2; SW_4-1437565-2
U12: Q65110A2395; LGM67K-G1J2-24-Z
U13: nc7sz125m5x; NC7SZ125M5X

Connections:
CLK_CRYSTAL_U1_8: C12.1, U1.8, U7.1
CLK_CRYSTAL_U1_9: C13.1, U1.9, U7.2
CLK_CRYSTAL_U1_12: C14.1, U1.12, U8.1
CLK_CRYSTAL_U1_13: C15.1, U1.13, U8.2
GND: C1.2, C2.2, C3.2, C4.2, C5.2, C6.2, C7.2, C8.2, C9.2, C10.2, C11.2, C12.2, C13.2, C14.2, C15.2, C16.2, C17.2, C18.2, C20.2, C21.2, C22.2, C23.2, C24.2, C25.2, C26.2, C27.2, C28.2, C29.2, C30.2, J1.2, R2.2, R9.2, R14.2, R16.2, R17.2, R20.2, R23.2, R25.2, U1.10, U1.19, U1.20, U1.27, U1.49, U1.74, U1.99, U2.4, U3.8, U4.9, U5.4, U6.4, U9.3, U9.PAD, U10.2, U12.C, U13.1, U13.3
NET_U1_14: R4.1, U1.14, U13.4
NET_U1_22: C9.1, C10.1, C11.1, F1.1, U1.21, U1.22
NET_U1_47: R7.1, U1.47, U5.6
NET_U1_48: R8.1, U1.48, U5.5
NET_U1_92: R5.1, U1.92, U6.6
NET_U1_93: R6.1, U1.93, U6.5
NET_U1_94: R9.1, U1.94
NET_U1_98: U11.3, U11.4
NET_U2_3: R10.1, U2.3
NET_U2_7: R12.1, U2.7
NET_U3_6: C17.1, U3.6
NET_U3_7: C19.1, I1.2, U3.7
NET_U3_9: C18.1, U3.9
NET_U3_10: C19.2, U3.10
NET_U3_11: R13.1, U3.11
NET_U4_3: U3.1, U4.3
NET_U4_4: U3.2, U4.4
NET_U4_5: U3.3, U4.5
NET_U4_6: U3.4, U4.6
NET_U5_3: R14.1, U5.3
NET_U6_1: R15.1, U6.1
NET_U6_2: R16.1, U6.2
NET_U6_3: R17.1, U6.3
NET_U9_1: C24.1, U9.1
NET_U9_6: R19.2, R20.1, U9.6
NET_U9_8: R18.1, U9.8
NET_U10_1: R22.1, R23.1, U10.1
NET_U10_3: R24.2, R25.1, U10.3
NET_U10_4: R21.1, U10.4, U13.2
NET_U11_1: R2.1, U11.1, U11.2
PROC_SPI1_MISO: U1.31, U2.2
PROC_SPI1_MOSI: U1.32, U2.5
PROC_SPI1_NSS: R11.1, U1.29, U2.1
PROC_SPI1_SCK: U1.30, U2.6
PROC_USART1_CTS: U1.70, U3.13
PROC_USART1_RX: U1.69, U3.16
PROC_USART1_TX: U1.68, U3.14
VCC_S1_12V8: C25.1, C28.1, C29.1, J1.1, R18.2, U9.4
VCC_TIER1_2V5: C1.1, C2.1, C3.1, C4.1, C5.1, C6.1, C7.1, C8.1, C16.1, C20.1, C21.1, C22.1, C23.1, C26.1, C27.1, C30.1, F1.2, I1.1, R4.2, R5.2, R6.2, R7.2, R8.2, R10.2, R11.2, R12.2, R13.2, R15.2, R19.1, R21.2, R22.2, R24.1, U1.6, U1.11, U1.28, U1.50, U1.75, U1.100, U2.8, U3.5, U3.12, U5.8, U6.7, U6.8, U9.5, U10.6, U13.5
